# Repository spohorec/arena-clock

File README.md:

# Mass Destruction Arena Clock

A simple and robust solution for combat robotics arena-side match clock. The clock consists of a PCB for power + logic, 2 sets of 3x 6" seven-segment digits (one for competitors, one for audience viewing), and a nucleo-L412KB for control. The clock is controlled via USB UART and a python gui.

## READMEs

[Firmware README](firmware/README.md)

[GUI README](gui/README.md)

[PCB README](pcb/README.md)

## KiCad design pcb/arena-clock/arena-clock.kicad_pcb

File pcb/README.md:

# Arena Clock PCB

This PCB project was made with Kicad 6.0

## Bill of Materials

TODO

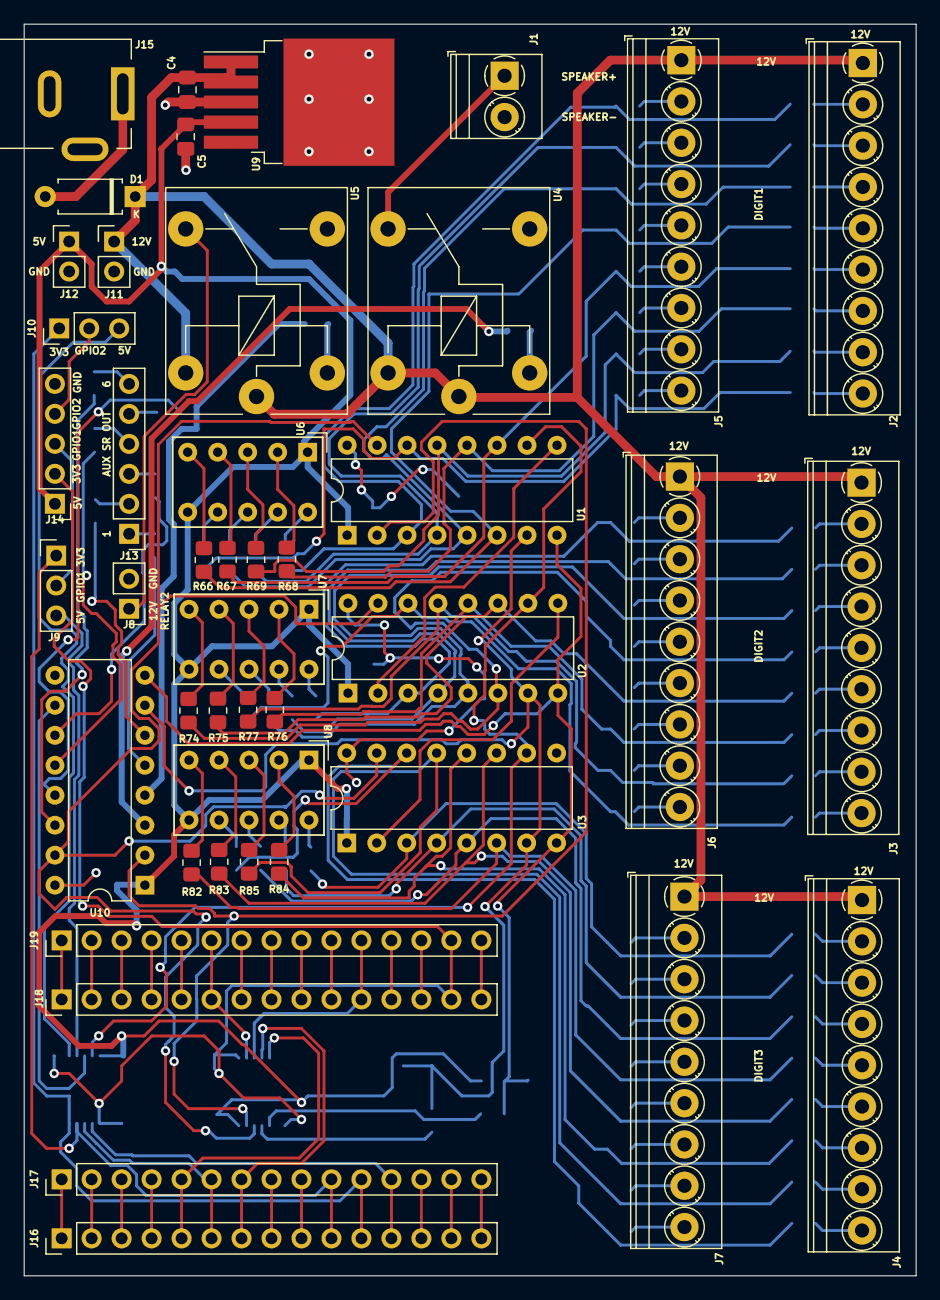
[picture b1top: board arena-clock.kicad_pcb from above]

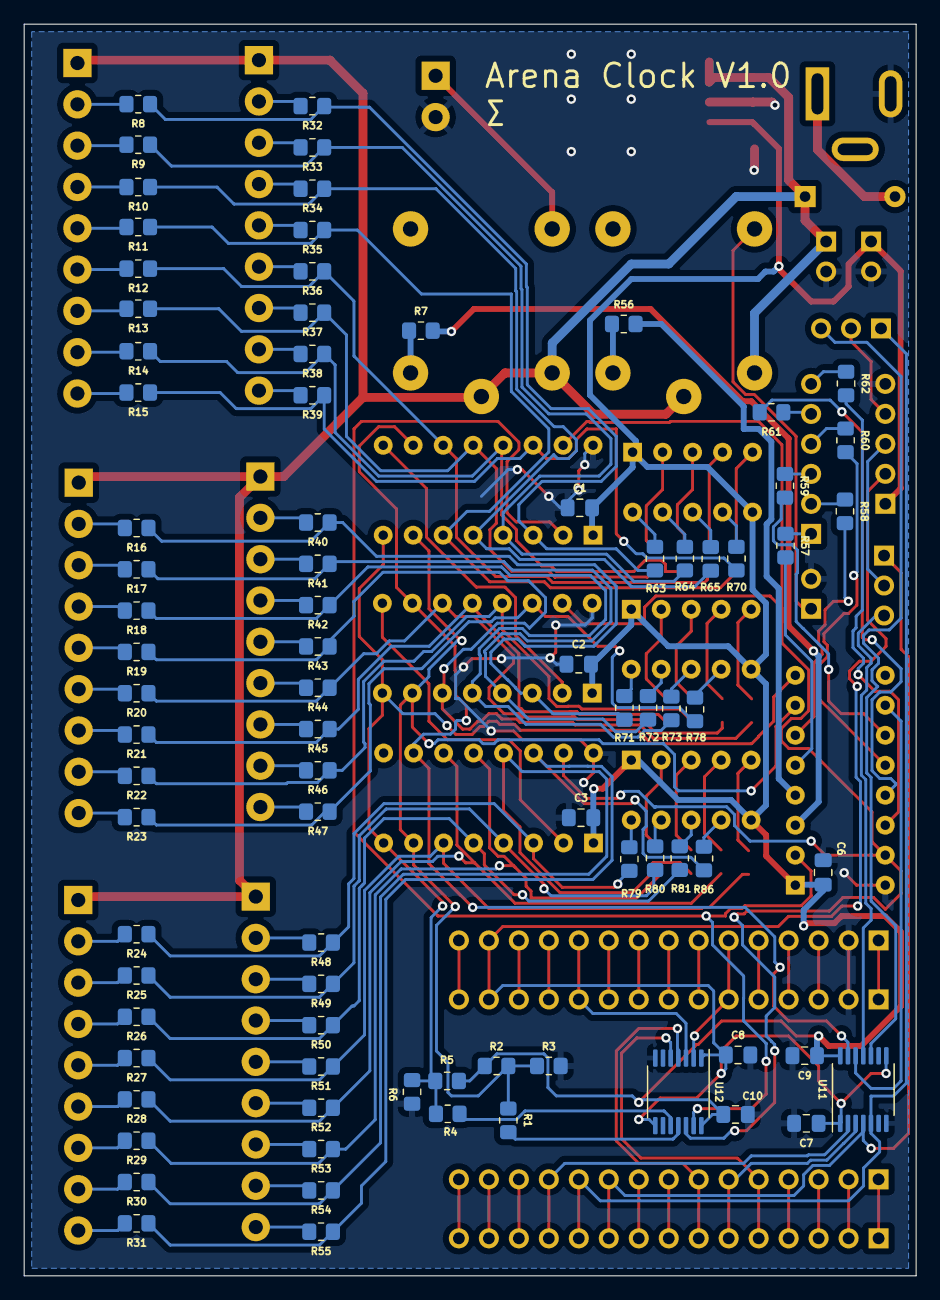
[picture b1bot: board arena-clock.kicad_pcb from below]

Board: 2 copper layers, 75.6 x 106.0 mm, 128 parts (84 on the bottom side), 141 nets.

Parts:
C1, C2, C3, C6: C_Small; C_0805_2012Metric_Pad1.18x1.45mm_HandSolder
C4, C5: 10u; C_0805_2012Metric_Pad1.18x1.45mm_HandSolder
C7, C8, C9, C10: 0.1u; C_0805_2012Metric_Pad1.18x1.45mm_HandSolder
D1: D_Schottky; D_A-405_P7.62mm_Horizontal
J1: SPEAKER ENABLE; TerminalBlock_Phoenix_PT-1,5-2-3.5-H_1x02_P3.50mm_Horizontal
J2: DIGIT1; TerminalBlock_Phoenix_PT-1,5-9-3.5-H_1x09_P3.50mm_Horizontal
J3: DIGIT2; TerminalBlock_Phoenix_PT-1,5-9-3.5-H_1x09_P3.50mm_Horizontal
J4: DIGIT3; TerminalBlock_Phoenix_PT-1,5-9-3.5-H_1x09_P3.50mm_Horizontal
J5: DIGIT4; TerminalBlock_Phoenix_PT-1,5-9-3.5-H_1x09_P3.50mm_Horizontal
J6: DIGIT5; TerminalBlock_Phoenix_PT-1,5-9-3.5-H_1x09_P3.50mm_Horizontal
J7: DIGIT6; TerminalBlock_Phoenix_PT-1,5-9-3.5-H_1x09_P3.50mm_Horizontal
J8: AUX 12V OUT; PinHeader_1x02_P2.54mm_Vertical
J9, J10: Conn_01x03_Male; PinHeader_1x03_P2.54mm_Vertical
J11: 12V POW CONN; PinHeader_1x02_P2.54mm_Vertical
J12: 5V POW CONN; PinHeader_1x02_P2.54mm_Vertical
J13: AUX SINK; PinHeader_1x06_P2.54mm_Vertical
J14: AUX GPIO; PinHeader_1x05_P2.54mm_Vertical
J15: Barrel_Jack; BarrelJack_Kycon_KLDX-0202-xC_Horizontal
J16: CN3 Breakout; PinHeader_1x15_P2.54mm_Vertical
J17: CN3; PinHeader_1x15_P2.54mm_Vertical
J18: CN4; PinHeader_1x15_P2.54mm_Vertical
J19: CN4 Breakout; PinHeader_1x15_P2.54mm_Vertical
R1, R4, R7, R56, R57, R58, R59, R60, R61, R62: 0; R_0805_2012Metric_Pad1.20x1.40mm_HandSolder
R2, R3, R5, R6: 100k; R_0805_2012Metric_Pad1.20x1.40mm_HandSolder
R8, R9, R10, R11, R12, R13, R14, R15, R16, R17, R18, R19, R20, R21, R22, R23, R24, R25, R26, R27, R28, R29, R30, R31, R32, R33, R34, R35, R36, R37, R38, R39, R40, R41, R42, R43, R44, R45, R46, R47, R48, R49, R50, R51, R52, R53, R54, R55: 15; R_0805_2012Metric_Pad1.20x1.40mm_HandSolder
R63, R64, R65, R66, R67, R68, R69, R70, R71, R72, R73, R74, R75, R76, R77, R78, R79, R80, R81, R82, R83, R84, R85, R86: 120; R_0805_2012Metric_Pad1.20x1.40mm_HandSolder
U1, U2, U3, U10: TPIC6595; DIP-16_W7.62mm
U4, U5: J107F1CS1212VDC.36; Relay_SPDT_Finder_36.11
U6, U7, U8: HDSP-7501; HDSP-A151
U9: BD50FD0WFP; TO-263-5_TabPin6
U11, U12: TXU0104; TSSOP-14_4.4x5mm_P0.65mm

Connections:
+3V3: C7.1, C8.1, J14.2, J18.14, J19.14, U11.1 (VCCA), U11.8 (OE), U12.1 (VCCA), U12.8 (OE)
+5V: C1.2, C2.2, C3.2, C5.1, C6.2, C9.1, C10.1, J12.1, J14.1, R2.1, R5.1, U1.1 (VCC), U2.1 (VCC), U3.1 (VCC), U6.1 (CA), U6.6 (CA), U7.1 (CA), U7.6 (CA), U8.1 (CA), U8.6 (CA), U9.4 (VO), U10.1 (VCC), U11.14 (VCCB), U12.14 (VCCB)
+12V: C4.1, D1.1 (K), J2.1, J3.1, J4.1, J5.1, J6.1, J7.1, J11.1, U4.11 (COM), U4.A2 (COIL+), U5.11 (COM), U5.A2 (COIL+), U9.1 (EN), U9.2 (VCC)
/auxillary_sr/AUX_SR_1: R7.2, U10.3 (DRAIN0)
/auxillary_sr/AUX_SR_2: R56.2, U10.4 (DRAIN1)
/auxillary_sr/AUX_SR_3: R57.2, U10.5 (DRAIN2)
/auxillary_sr/AUX_SR_4: R58.2, U10.6 (DRAIN3)
/auxillary_sr/AUX_SR_5: R59.2, U10.11 (DRAIN4)
/auxillary_sr/AUX_SR_6: R60.2, U10.12 (DRAIN5)
/auxillary_sr/AUX_SR_7: R61.2, U10.13 (DRAIN6)
/auxillary_sr/AUX_SR_8: R62.2, U10.14 (DRAIN7)
/board_output/DIGIT1_1: R8.1, R32.1, R63.1, U1.3 (DRAIN0)
/board_output/DIGIT1_2: R9.1, R33.1, R64.1, U1.4 (DRAIN1)
/board_output/DIGIT1_3: R10.1, R34.1, R65.1, U1.5 (DRAIN2)
/board_output/DIGIT1_4: R11.1, R35.1, R66.1, U1.6 (DRAIN3)
/board_output/DIGIT1_5: R12.1, R36.1, R67.1, U1.11 (DRAIN4)
/board_output/DIGIT1_6: R13.1, R37.1, R68.1, U1.12 (DRAIN5)
/board_output/DIGIT1_7: R14.1, R38.1, R69.1, U1.13 (DRAIN6)
/board_output/DIGIT1_8: R15.1, R39.1, R70.1, U1.14 (DRAIN7)
/board_output/DIGIT2_1: R16.1, R40.1, R71.1, U2.3 (DRAIN0)
/board_output/DIGIT2_2: R17.1, R41.1, R72.1, U2.4 (DRAIN1)
/board_output/DIGIT2_3: R18.1, R42.1, R73.1, U2.5 (DRAIN2)
/board_output/DIGIT2_4: R19.1, R43.1, R74.1, U2.6 (DRAIN3)
/board_output/DIGIT2_5: R20.1, R44.1, R75.1, U2.11 (DRAIN4)
/board_output/DIGIT2_6: R21.1, R45.1, R76.1, U2.12 (DRAIN5)
/board_output/DIGIT2_7: R22.1, R46.1, R77.1, U2.13 (DRAIN6)
/board_output/DIGIT2_8: R23.1, R47.1, R78.1, U2.14 (DRAIN7)
/board_output/DIGIT3_1: R24.1, R48.1, R79.1, U3.3 (DRAIN0)
/board_output/DIGIT3_2: R25.1, R49.1, R80.1, U3.4 (DRAIN1)
/board_output/DIGIT3_3: R26.1, R50.1, R81.1, U3.5 (DRAIN2)
/board_output/DIGIT3_4: R27.1, R51.1, R82.1, U3.6 (DRAIN3)
/board_output/DIGIT3_5: R28.1, R52.1, R83.1, U3.11 (DRAIN4)
/board_output/DIGIT3_6: R29.1, R53.1, R84.1, U3.12 (DRAIN5)
/board_output/DIGIT3_7: R30.1, R54.1, R85.1, U3.13 (DRAIN6)
/board_output/DIGIT3_8: R31.1, R55.1, R86.1, U3.14 (DRAIN7)
/level_shifters/IN_3V3_1: J18.6, J19.6, U12.2 (A1)
/level_shifters/IN_3V3_2: J18.11, J19.11, U12.3 (A2)
/level_shifters/IN_3V3_3: J16.7, J17.7, U12.4 (A3)
/level_shifters/IN_3V3_4: J16.5, J17.5, U12.5 (A4)
/level_shifters/IN_3V3_5: J16.12, J17.12, U11.2 (A1)
/level_shifters/IN_3V3_6: J16.6, J17.6, U11.3 (A2)
/level_shifters/IN_3V3_7: J9.1, J16.10, J17.10, U11.4 (A3)
/level_shifters/IN_3V3_8: J10.1, J16.11, J17.11, U11.5 (A4)
/level_shifters/OUT_5V_1: U1.2 (SER_IN), U10.2 (SER_IN), U12.13 (B1)
/level_shifters/OUT_5V_2: U1.15 (SRCK), U2.15 (SRCK), U3.15 (SRCK), U10.15 (SRCK), U12.12 (B2)
/level_shifters/OUT_5V_3: R1.2, U12.11 (B3)
/level_shifters/OUT_5V_4: R4.2, U12.10 (B4)
/level_shifters/OUT_5V_5: U1.10 (RCK), U2.10 (RCK), U3.10 (RCK), U11.13 (B1)
/level_shifters/OUT_5V_6: U10.10 (RCK), U11.12 (B2)
/level_shifters/OUT_5V_7: J9.3, U11.11 (B3)
/level_shifters/OUT_5V_8: J10.3, U11.10 (B4)
/nCLR_PULLED: R1.1, R2.2, R3.1, U1.7 (CLR), U2.7 (CLR), U3.7 (CLR), U10.7 (CLR)
/nOE_PULLED: R4.1, R5.2, R6.1, U1.8 (G), U2.8 (G), U3.8 (G), U10.8 (G)
GND: C1.1, C2.1, C3.1, C4.2, C5.2, C6.1, C7.2, C8.2, C9.2, C10.2, J1.2, J8.2, J11.2, J12.2, J14.5, J15.2, J18.2, J19.2, R3.2, R6.2, U1.16 (GND), U2.16 (GND), U3.16 (GND), U9.3 (GND), U9.6, U10.16 (GND), U11.7 (GND), U12.7 (GND)
unnamed: D1.2 (A), J15.1
unnamed: J1.1, U4.12 (NO)
unnamed: J2.2, R8.2
unnamed: J2.3, R9.2
unnamed: J2.4, R10.2
unnamed: J2.5, R11.2
unnamed: J2.6, R12.2
unnamed: J2.7, R13.2
unnamed: J2.8, R14.2
unnamed: J2.9, R15.2
unnamed: J3.2, R16.2
unnamed: J3.3, R17.2
unnamed: J3.4, R18.2
unnamed: J3.5, R19.2
unnamed: J3.6, R20.2
unnamed: J3.7, R21.2
unnamed: J3.8, R22.2
unnamed: J3.9, R23.2
unnamed: J4.2, R24.2
unnamed: J4.3, R25.2
unnamed: J4.4, R26.2
unnamed: J4.5, R27.2
unnamed: J4.6, R28.2
unnamed: J4.7, R29.2
unnamed: J4.8, R30.2
unnamed: J4.9, R31.2
unnamed: J5.2, R32.2
unnamed: J5.3, R33.2
unnamed: J5.4, R34.2
unnamed: J5.5, R35.2
unnamed: J5.6, R36.2
unnamed: J5.7, R37.2
unnamed: J5.8, R38.2
unnamed: J5.9, R39.2
unnamed: J6.2, R40.2
unnamed: J6.3, R41.2
unnamed: J6.4, R42.2
unnamed: J6.5, R43.2
unnamed: J6.6, R44.2
unnamed: J6.7, R45.2
unnamed: J6.8, R46.2
unnamed: J6.9, R47.2
unnamed: J7.2, R48.2
unnamed: J7.3, R49.2
unnamed: J7.4, R50.2
unnamed: J7.5, R51.2
unnamed: J7.6, R52.2
unnamed: J7.7, R53.2
unnamed: J7.8, R54.2
unnamed: J7.9, R55.2
unnamed: J8.1, U5.12 (NO)
unnamed: J10.2, J14.4
unnamed: J13.1, R57.1
unnamed: J13.2, R58.1
unnamed: J13.3, R59.1
unnamed: J13.4, R60.1
unnamed: J13.5, R61.1
unnamed: J13.6, R62.1
unnamed: J9.2, J14.3
unnamed: R7.1, U4.A1 (COIL-)
unnamed: R56.1, U5.A1 (COIL-)
unnamed: R63.2, U6.10 (A)
unnamed: R64.2, U6.9 (B)
unnamed: R65.2, U6.8 (C)
unnamed: R66.2, U6.5 (D)
unnamed: R67.2, U6.4 (E)
unnamed: R68.2, U6.2 (F)
unnamed: R69.2, U6.3 (G)
unnamed: R70.2, U6.7 (DP)
unnamed: R71.2, U7.10 (A)
unnamed: R72.2, U7.9 (B)
unnamed: R73.2, U7.8 (C)
unnamed: R74.2, U7.5 (D)
unnamed: R75.2, U7.4 (E)
unnamed: R76.2, U7.2 (F)
unnamed: R77.2, U7.3 (G)
unnamed: R78.2, U7.7 (DP)
unnamed: R79.2, U8.10 (A)
unnamed: R80.2, U8.9 (B)
unnamed: R81.2, U8.8 (C)
unnamed: R82.2, U8.5 (D)
unnamed: R83.2, U8.4 (E)
unnamed: R84.2, U8.2 (F)
unnamed: R85.2, U8.3 (G)
unnamed: R86.2, U8.7 (DP)
unnamed: U1.9 (SER_OUT), U2.2 (SER_IN)
unnamed: U2.9 (SER_OUT), U3.2 (SER_IN)

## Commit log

2023-12-09 PCB as sent to OSHPark 11/19/2023
2023-12-09 [Cube] Add patch to generated sources to add call to MainLoop. Call patch from the generation script.
2023-12-09 Add README
2023-12-09 [Commands] Add command proccessor to route commands received over UART and set up the response.
2023-12-09 Update main loop to use timer state machine and command processor. Add UART tx and rx handling.
2023-12-09 Add gitignore
2023-12-09 Some organizational updates to gui. No functional changes.
2023-12-09 Initial GUI
2023-12-09 Add GPIO pin driver
2023-12-09 Add platform.ini and cube project. TODO make sources generate with pio build.
2023-12-09 Check cube sources on build and regenerate if out of date.
2023-12-09 [Cube] Add UART interrupt to configuration. Decrease baud rate for UART to 9600.
2023-12-09 Add generated cube source directories to gitignore
2023-12-09 [Timer] Add timer state machine and digit setting capability
2023-12-09 Add shift register driver. Used primarily for driving the seven segment displays
2023-12-09 Add main loop. Currently implemeneted with a countdown from one hundred for testing.
2023-12-09 Add seven segment driver which sets up the segment structs
2023-12-09 Move platformio firmware to firmware subdirectory
2023-12-09 Add some documentation in READMEs.
2023-12-09 [GUI] Add helper function in the Timer class to handle serial commands from the GUI to the nucleo.
2023-12-09 [Timer] Upgrade to 16b int for timer. Add a second byte to the command arguments. Update GUI to use two-byte argument.
2023-12-09 Update gitignore after moving firmware sources to subdirectory
2023-12-09 Add kicad backup directory to gitignore
2023-12-09 Update kicad schematic and layout with metadata (release date, title, company) and export pdfs as sent to mfg on 11/19.
2024-08-24 Fix typos causing error in gui
